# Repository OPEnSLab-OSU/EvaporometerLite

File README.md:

# EvaporometerLite
This repository contains all the files needed to recreate the Evaporometer LITE.
# How to Setup
Follow assembly guide located in the documentation folder. 

# Directory Layout
Documentation contains assembly procedure, BOM.

CAD contains .stl and .step files of 3D printed components. 

PCB contains PCB design.

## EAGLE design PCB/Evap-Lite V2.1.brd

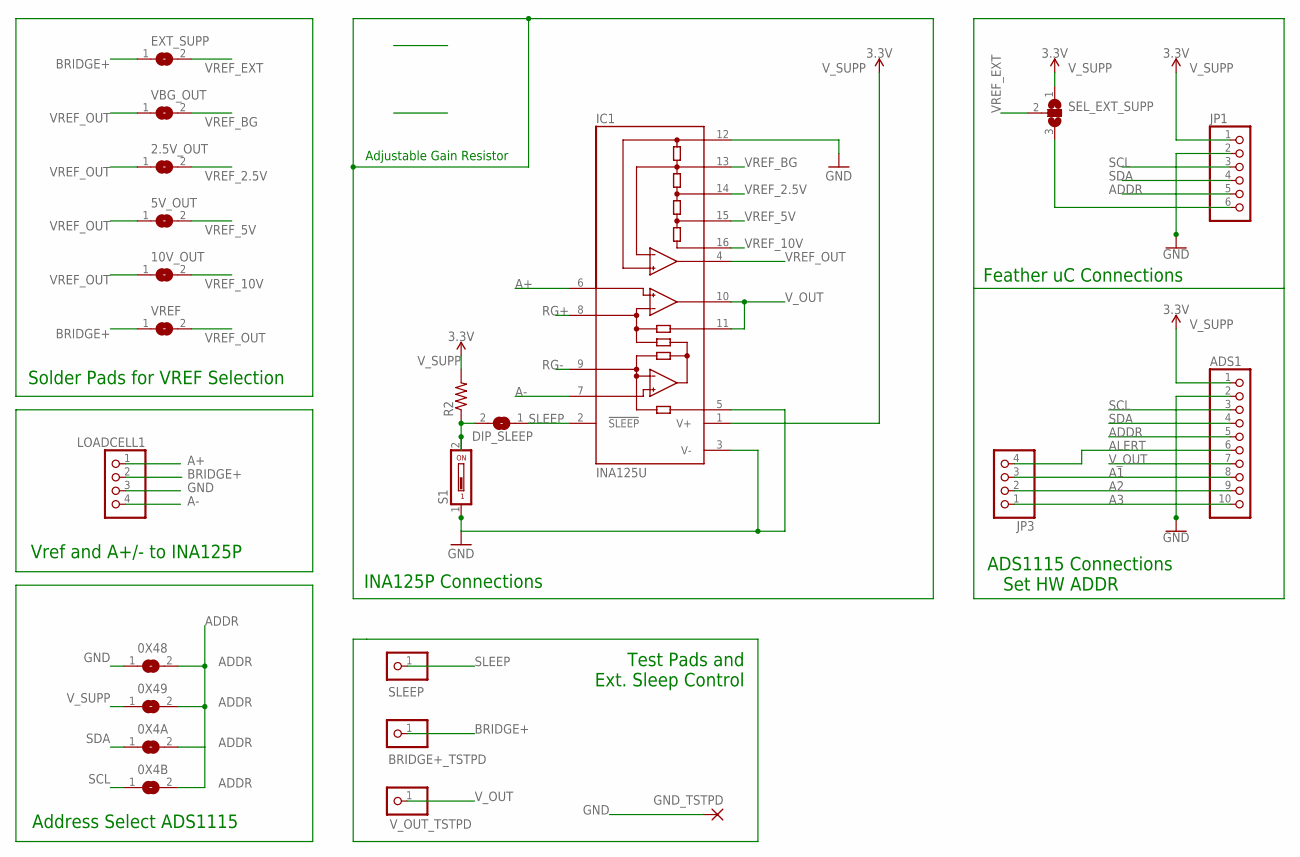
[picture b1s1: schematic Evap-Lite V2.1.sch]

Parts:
0X4A, 0X4B, 0X48, 0X49, 2.5V_OUT, 5V_OUT, 10V_OUT: SJ
ADS1: PINHD-1X10; 1X10
BRIDGE+_TSTPD: PINHD-1X1; 1X01
DIP_SLEEP: SJ
EXT_SUPP: SJ
GND_TSTPD: WIREPADSMD2,54-5,08; SMD2,54-5,08
IC1: INA125U; SO16-1
JP1: PINHD-1X6; 1X06
JP3: PINHD-1X4; 1X04
LOADCELL1: PINHD-1X4; 1X04
R2: R-US_R1206; R1206
S1: DS01; DS-01
SEL_EXT_SUPP: SJ2WW; SJ_2W
SLEEP: PINHD-1X1; 1X01
VBG_OUT: SJ
VREF: SJ
V_OUT_TSTPD: PINHD-1X1; 1X01

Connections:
A1: ADS1.8, JP3.3
A2: ADS1.9, JP3.2
A3: ADS1.10, JP3.1
A+: IC1.6 (+IN), LOADCELL1.1
A-: IC1.7 (-IN), LOADCELL1.4
ADDR: 0X4A.2, 0X4B.2, 0X48.2, 0X49.2, ADS1.5, JP1.5
ALERT: ADS1.6, JP3.4
BRIDGE+: BRIDGE+_TSTPD.1, EXT_SUPP.1, LOADCELL1.2, VREF.1
GND: 0X48.1, ADS1.2, GND_TSTPD.1, IC1.3 (V-), IC1.5 (REF), IC1.12 (REFCOM), JP1.2, LOADCELL1.3, S1.1
unnamed: JP1.6, SEL_EXT_SUPP.3
unnamed: DIP_SLEEP.2, R2.1, S1.2
RG+: IC1.8 (RG)
RG-: IC1.9 (RG)
SCL: 0X4B.1, ADS1.3, JP1.3
SDA: 0X4A.1, ADS1.4, JP1.4
SLEEP: DIP_SLEEP.1, IC1.2 (!SLEEP), SLEEP.1
VREF_2.5V: 2.5V_OUT.2, IC1.14 (REF2.5)
VREF_5V: 5V_OUT.2, IC1.15 (REF5)
VREF_10V: 10V_OUT.2, IC1.16 (REF10)
VREF_BG: IC1.13 (REFBG), VBG_OUT.2
VREF_EXT: EXT_SUPP.2, SEL_EXT_SUPP.2
VREF_OUT: 2.5V_OUT.1, 5V_OUT.1, 10V_OUT.1, IC1.4 (REFOUT), VBG_OUT.1, VREF.2
V_OUT: ADS1.7, IC1.10 (OUT), IC1.11 (SENSE), V_OUT_TSTPD.1
V_SUPP: 0X49.1, ADS1.1, IC1.1 (V+), JP1.1, R2.2, SEL_EXT_SUPP.1

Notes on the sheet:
Vref and A+/- to INA125P
Solder Pads for VREF Selection
Feather uC Connections
Address Select ADS1115
ADS1115 Connections Set HW ADDR
Adjustable Gain Resistor
INA125P Connections
Test Pads and Ext. Sleep Control

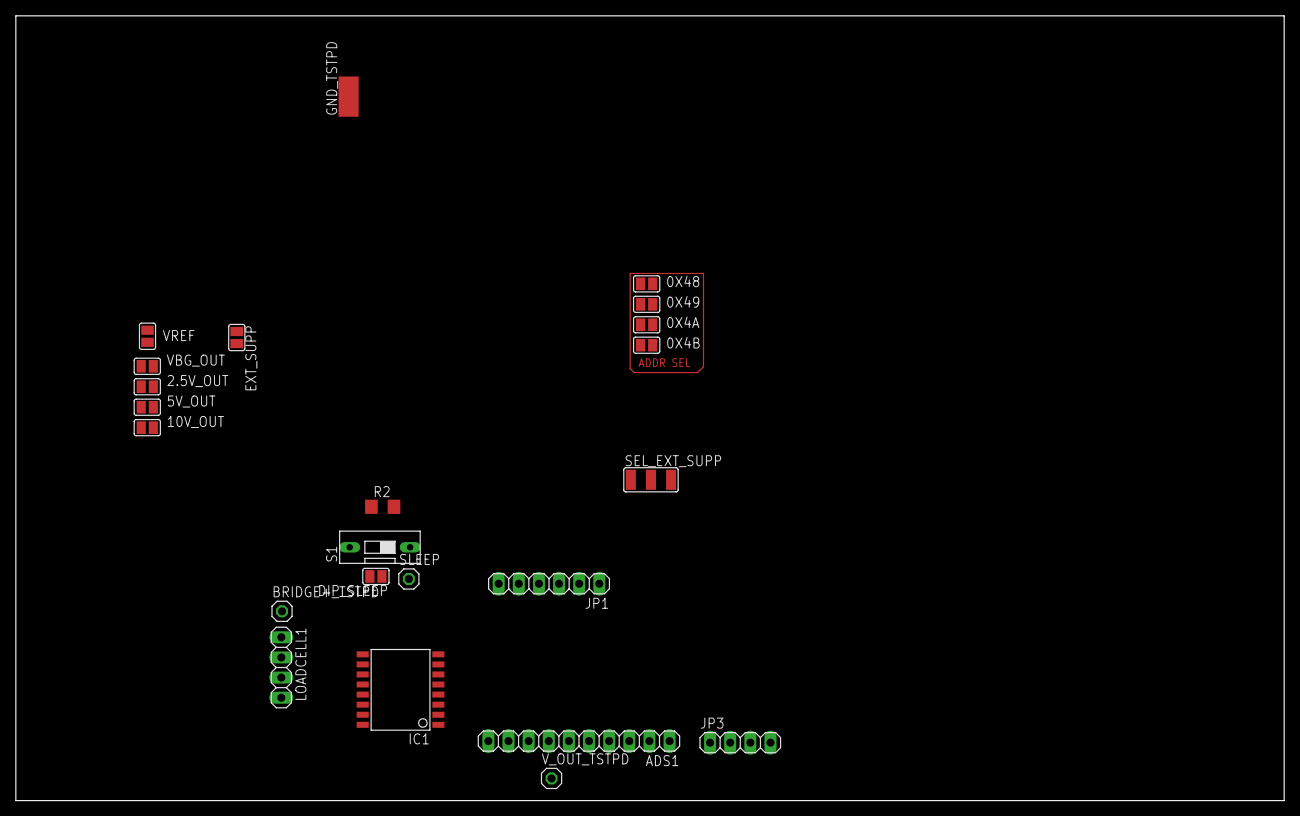
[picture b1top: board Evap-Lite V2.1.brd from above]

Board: 2 copper layers, 160.0 x 99.0 mm, 23 parts (0 on the bottom side), 22 nets.

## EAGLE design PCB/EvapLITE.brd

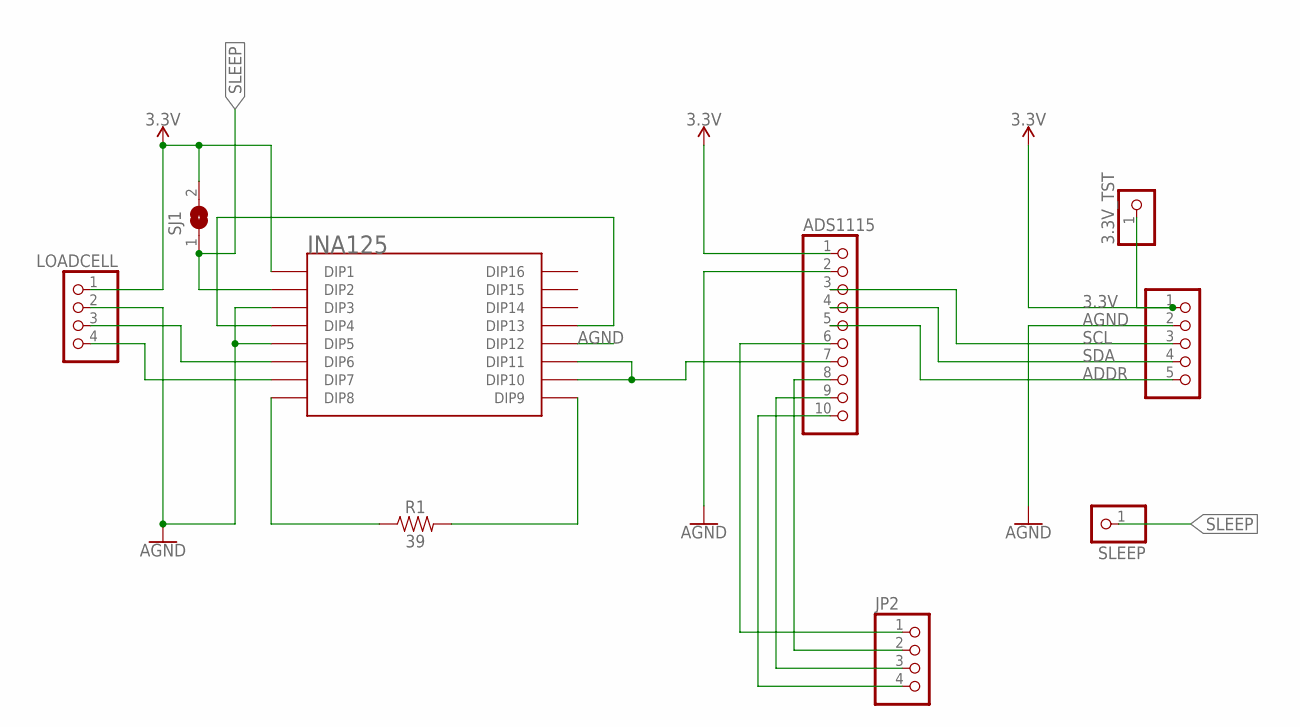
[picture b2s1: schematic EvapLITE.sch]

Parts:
3.3V_TST: PINHD-1X1; 1X01
ADS1115: PINHD-1X10; 1X10
I2C: PINHD-1X5; 1X05
INA125: 16-PIN_DIP
JP2: PINHD-1X4; 1X04
LOADCELL: PINHD-1X4; 1X04
R1: 39; AXIAL-0.3
SJ1: SJ
SLEEP: PINHD-1X1; 1X01

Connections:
3.3V: 3.3V_TST.1, ADS1115.1, I2C.1, INA125.DIP1, LOADCELL.1, SJ1.2
ADDR: ADS1115.5, I2C.5
AGND: ADS1115.2, I2C.2, INA125.DIP3, INA125.DIP5, INA125.DIP12, LOADCELL.2
unnamed: INA125.DIP4, INA125.DIP13
unnamed: INA125.DIP6, LOADCELL.3
unnamed: INA125.DIP7, LOADCELL.4
unnamed: INA125.DIP8, R1.P$1 (1)
unnamed: INA125.DIP9, R1.P$2 (2)
unnamed: ADS1115.7, INA125.DIP10, INA125.DIP11
unnamed: ADS1115.8, JP2.2
unnamed: ADS1115.9, JP2.3
unnamed: ADS1115.10, JP2.4
unnamed: ADS1115.6, JP2.1
SCL: ADS1115.3, I2C.3
SDA: ADS1115.4, I2C.4
SLEEP: INA125.DIP2, SJ1.1, SLEEP.1

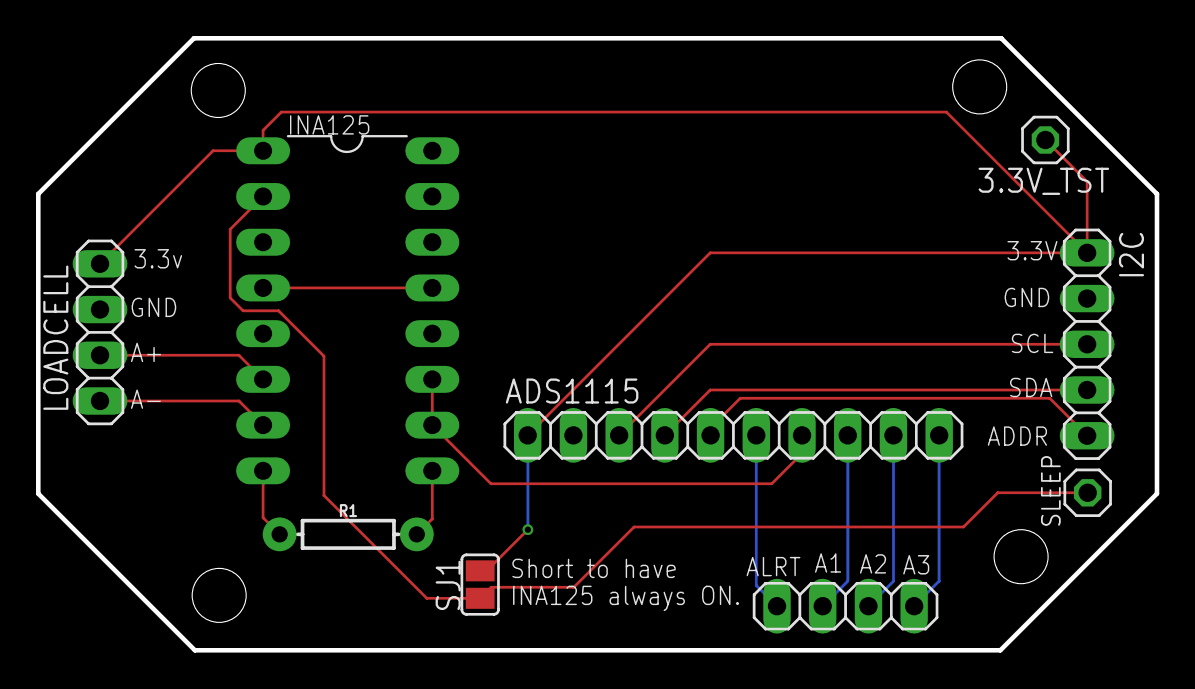
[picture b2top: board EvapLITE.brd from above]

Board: 2 copper layers, 62.2 x 34.0 mm, 9 parts (0 on the bottom side), 16 nets.

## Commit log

2019-04-15 Create EvaporometerWeightTest
2019-04-23 Coupler CAD file
2019-04-23 Uploaded more CAD files
2019-04-23 PCB board/Ads 1115
2019-04-24 Uploaded stl CAD files
2019-05-31 Loadcell Testing Upload
2019-06-10 Added Temperature dependency test
2019-07-29 Voltage measurements
2019-07-29 voltage measurement
2019-10-07 Removing obsolete code
2019-10-07 removed obsolete code
2019-10-07 Update EvapLite.ino
    Removed section of code that would remove stored data from SD card
2019-10-07 added schematic and board files for EvapLite PCB

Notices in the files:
parts and their libraries:
SparkFun-PowerSymbols: Licensing: Creative Commons ShareAlike 4.0 International - https://creativecommons.org/licenses/by-sa/4.0
